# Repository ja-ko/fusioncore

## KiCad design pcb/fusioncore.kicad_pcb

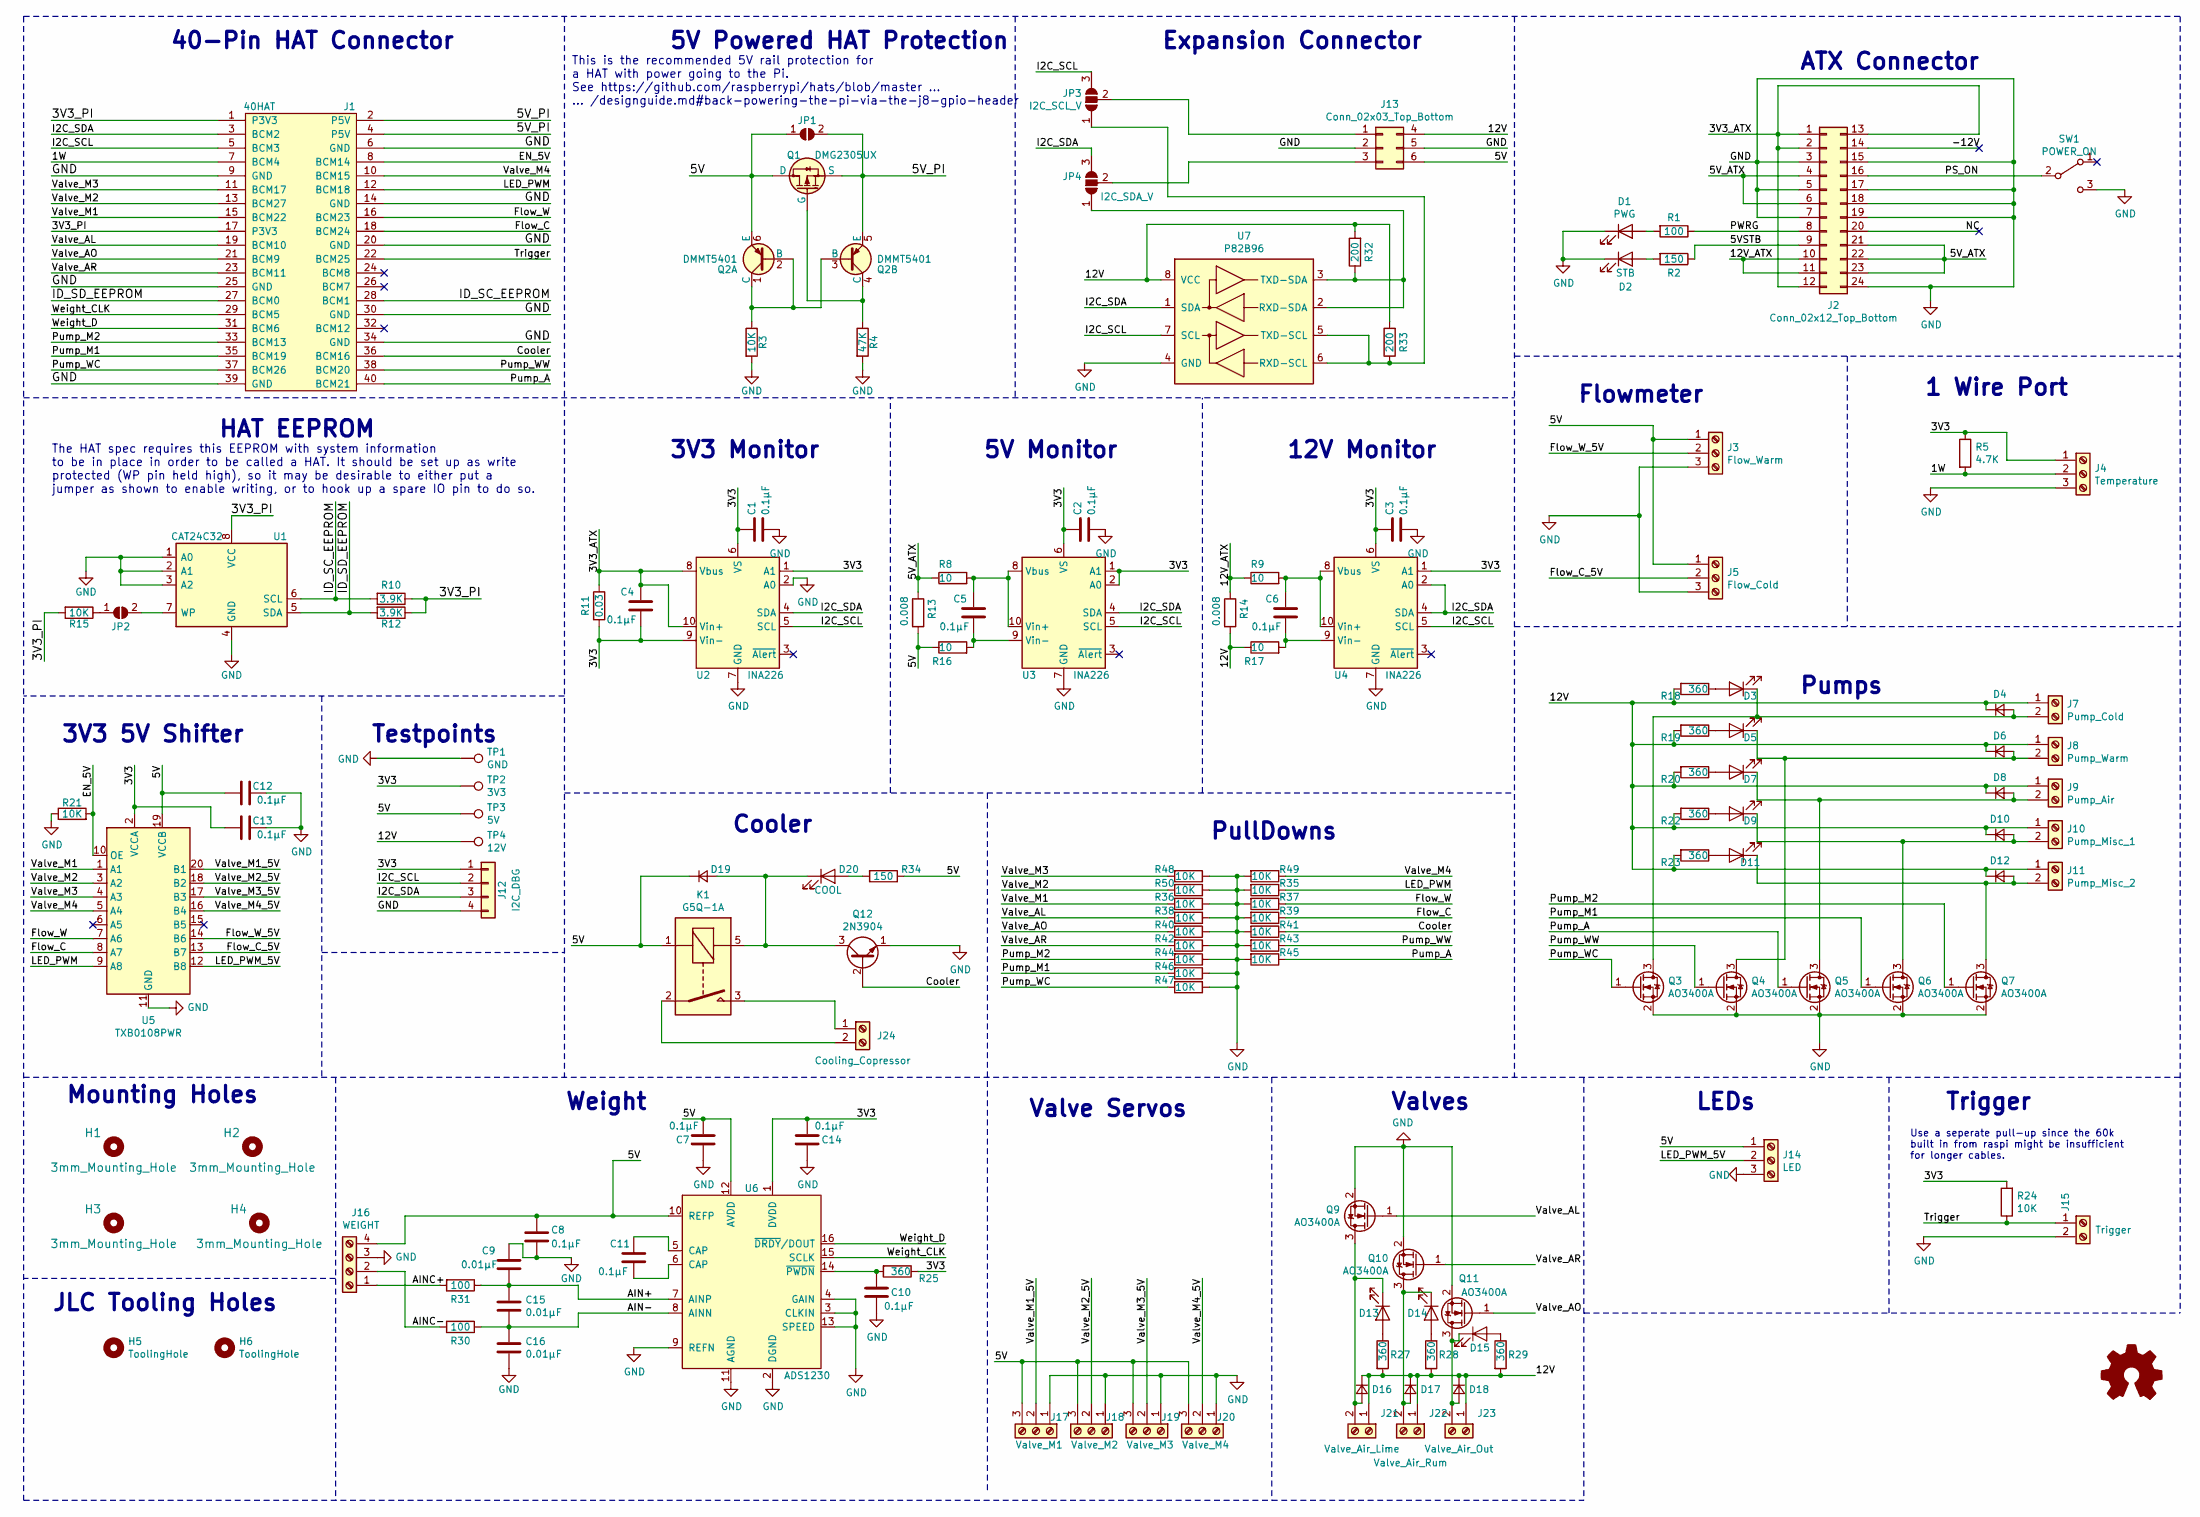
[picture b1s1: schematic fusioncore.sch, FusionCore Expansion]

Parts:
C1, C2, C3, C4, C5, C6, C7, C8, C10, C11, C12, C13, C14: 0.1μF; C_0805_2012Metric_Pad1.15x1.40mm_HandSolder; LCSC C49678
C9, C15, C16: 0.01μF; C_0402_1005Metric; LCSC C15195
D1: PWG; LED_0603_1608Metric_Pad1.05x0.95mm_HandSolder; LCSC C72043
D2: STB; LED_0805_2012Metric_Pad1.15x1.40mm_HandSolder; LCSC C2296
D3, D5, D7, D9, D11, D13, D14, D15: LED; LED_0603_1608Metric_Pad1.05x0.95mm_HandSolder; LCSC C72041
D4, D6, D8, D10, D12: D_Small; D_SMA; LCSC C22452
D16, D17, D18, D19: D; D_SMA; LCSC C22452
D20: COOL; LED_0805_2012Metric_Pad1.15x1.40mm_HandSolder; LCSC C2296
H1, H2, H3, H4: 3mm_Mounting_Hole; NPTH_3mm_ID
H5, H6: ToolingHole; JLC_Tooling_Hole
J1: 40HAT; PinSocket_2x20_P2.54mm_Vertical; Digikey 952-2150-ND‎
J2: Conn_02x12_Top_Bottom; Molex_Mini-Fit_Jr_5566-24A_2x12_P4.20mm_Vertical; Digikey WM3811-ND‎
J3: Flow_Warm; TerminalBlock_Phoenix_PT-1,5-3-5.0-H_1x03_P5.00mm_Horizontal; Digikey 277-1578-ND‎
J4: Temperature; TerminalBlock_Phoenix_PT-1,5-2-3.5-H_1x03_P3.50mm_Diagonal; Digikey 277-1780-ND
J5: Flow_Cold; TerminalBlock_Phoenix_PT-1,5-3-5.0-H_1x03_P5.00mm_Horizontal; Digikey 277-1578-ND‎
J7: Pump_Cold; TerminalBlock_Phoenix_PT-1,5-2-5.0-H_1x02_P5.00mm_Horizontal; Digikey 277-1667-ND
J8: Pump_Warm; TerminalBlock_Phoenix_PT-1,5-2-5.0-H_1x02_P5.00mm_Horizontal; Digikey 277-1667-ND
J9: Pump_Air; TerminalBlock_Phoenix_PT-1,5-2-5.0-H_1x02_P5.00mm_Horizontal; Digikey 277-1667-ND
J10: Pump_Misc_1; TerminalBlock_Phoenix_PT-1,5-2-5.0-H_1x02_P5.00mm_Horizontal; Digikey 277-1667-ND
J11: Pump_Misc_2; TerminalBlock_Phoenix_PT-1,5-2-5.0-H_1x02_P5.00mm_Horizontal; Digikey 277-1667-ND
J12: I2C_DBG; PinHeader_1x04_P2.54mm_Vertical; Digikey 732-5317-ND
J13: Conn_02x03_Top_Bottom; Molex_Micro-Fit_3.0_43045-0612_2x03_P3.00mm_Vertical; Digikey WM1791-ND
J14: LED; TerminalBlock_Phoenix_PT-1,5-3-5.0-H_1x03_P5.00mm_Horizontal; Digikey 277-1578-ND‎
J15: Trigger; TerminalBlock_Phoenix_PT-1,5-2-3.5-H_1x02_P3.50mm_Diagonal; Digikey 277-1779-ND
J16: WEIGHT; TerminalBlock_Phoenix_PT-1,5-4-5.0-H_1x04_P5.00mm_Horizontal
J17: Valve_M1; TerminalBlock_Phoenix_PT-1,5-3-5.0-H_1x03_P5.00mm_Horizontal; Digikey 277-1578-ND‎
J18: Valve_M2; TerminalBlock_Phoenix_PT-1,5-3-5.0-H_1x03_P5.00mm_Horizontal; Digikey 277-1578-ND‎
J19: Valve_M3; TerminalBlock_Phoenix_PT-1,5-3-5.0-H_1x03_P5.00mm_Horizontal; Digikey 277-1578-ND‎
J20: Valve_M4; TerminalBlock_Phoenix_PT-1,5-3-5.0-H_1x03_P5.00mm_Horizontal; Digikey 277-1578-ND‎
J21: Valve_Air_Lime; TerminalBlock_Phoenix_PT-1,5-2-5.0-H_1x02_P5.00mm_Horizontal; Digikey 277-1667-ND
J22: Valve_Air_Rum; TerminalBlock_Phoenix_PT-1,5-2-5.0-H_1x02_P5.00mm_Horizontal; Digikey 277-1667-ND
J23: Valve_Air_Out; TerminalBlock_Phoenix_PT-1,5-2-5.0-H_1x02_P5.00mm_Horizontal; Digikey 277-1667-ND
J24: Cooling_Copressor; TerminalBlock_Phoenix_PT-1,5-2-5.0-H_1x02_P5.00mm_Horizontal
JP1, JP2: SolderJumper_2_Open; SolderJumper-2_P1.3mm_Open_Pad1.0x1.5mm
JP3: I2C_SCL_V; SolderJumper-3_P1.3mm_Open_Pad1.0x1.5mm
JP4: I2C_SDA_V; SolderJumper-3_P1.3mm_Open_Pad1.0x1.5mm
K1: G5Q-1A; Relay_SPST_Omron-G5Q-1A; Digikey ‎Z6367-ND‎
Q1: DMG2305UX; SOT-23; LCSC C144153
Q2: DMMT5401; SOT-23-6_Handsoldering; LCSC C154733
Q3, Q4, Q5, Q6, Q7, Q9, Q10, Q11: AO3400A; SOT-23; LCSC C20917
Q12: 2N3904; SOT-23; LCSC C18536
R1, R30, R31: 100; R_0805_2012Metric_Pad1.15x1.40mm_HandSolder; LCSC C17408
R2, R34: 150; R_0805_2012Metric_Pad1.15x1.40mm_HandSolder; LCSC C17471
R3, R15, R21, R24: 10K; R_0805_2012Metric_Pad1.15x1.40mm_HandSolder; LCSC C17414
R4: 47K; R_0805_2012Metric_Pad1.15x1.40mm_HandSolder; LCSC C17713
R5: 4.7K; R_0805_2012Metric_Pad1.15x1.40mm_HandSolder; LCSC C17673
R8, R9, R16, R17: 10; R_0805_2012Metric_Pad1.15x1.40mm_HandSolder; LCSC C17415
R10, R12: 3.9K; R_0805_2012Metric_Pad1.15x1.40mm_HandSolder; LCSC C17614
R11: 0.03; R_0805_2012Metric_Pad1.15x1.40mm_HandSolder; LCSC C247605
R13, R14: 0.008; R_2512_6332Metric_Pad1.52x3.35mm_HandSolder; LCSC C76241
R18, R19, R20, R22, R23, R25, R27, R28, R29: 360; R_0603_1608Metric_Pad1.05x0.95mm_HandSolder; LCSC C25194
R32, R33: 200; R_0805_2012Metric_Pad1.15x1.40mm_HandSolder; LCSC C17540
R35, R36, R37, R38, R39, R40, R41, R42, R43, R44, R45, R46, R47, R48, R49, R50: 10K; R_0402_1005Metric; LCSC C25744
SW1: POWER_ON; SW_CuK_JS202011CQN_DPDT_Straight; Digikey 401-2001-ND
TP1: GND; TestPoint_THTPad_D2.0mm_Drill1.0mm
TP2: 3V3; TestPoint_THTPad_D2.0mm_Drill1.0mm
TP3: 5V; TestPoint_THTPad_D2.0mm_Drill1.0mm
TP4: 12V; TestPoint_THTPad_D2.0mm_Drill1.0mm
U1: CAT24C32; SOIC-8_3.9x4.9mm_P1.27mm; LCSC C81193
U2, U3, U4: INA226; VSSOP-10_3x3mm_P0.5mm; LCSC C49851
U5: TXB0108PWR; TSSOP-20_4.4x6.5mm_P0.65mm; LCSC C53406
U6: ADS1230; TSSOP-16_4.4x5mm_P0.65mm; LCSC C58052
U7: P82B96; SOIC-8_3.9x4.9mm_P1.27mm; LCSC C32103

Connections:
/1W: J1.7 (BCM4), J4.2, R5.2
/3V3: C1.2, C2.2, C3.2, C4.1, C13.2, C14.2, J4.1, J12.1, R5.1, R11.2, R24.2, R25.1, TP2.1, U2.1 (A1), U2.6 (VS), U2.9 (Vin-), U3.1 (A1), U3.2 (A0), U3.6 (VS), U4.1 (A1), U4.6 (VS), U5.2 (VCCA), U6.1 (DVDD)
/3V3_ATX: C4.2, J2.1, J2.2, J2.12, J2.13, R11.1, U2.8 (Vbus), U2.10 (Vin+)
/3V3_PI: J1.1 (P3V3), J1.17 (P3V3), R10.1, R12.1, R15.2, U1.8 (VCC)
/5V: C7.2, C8.2, C12.2, D19.1 (K), J3.1, J5.1, J13.6, J14.1, J16.4, J17.3, J18.3, J19.3, J20.3, JP1.1 (A), K1.1, Q1.3 (D), Q2.6 (E), R13.2, R16.1, R34.1, TP3.1, U5.19 (VCCB), U6.10 (REFP), U6.12 (AVDD)
/5VSTB: J2.9, R2.1
/5V_ATX: J2.4, J2.6, J2.21, J2.22, J2.23, R8.1, R13.1
/5V_PI: J1.2 (P5V), J1.4 (P5V), JP1.2 (B), Q1.2 (S), Q2.5 (E)
/12V: D4.1 (K), D6.1 (K), D8.1 (K), D10.1 (K), D12.1 (K), D16.1 (K), D17.1 (K), D18.1 (K), J7.1, J8.1, J9.1, J10.1, J11.1, J13.4, J21.1, J22.1, J23.1, R14.2, R17.1, R18.2, R19.2, R20.2, R22.2, R23.2, R27.2, R28.2, R29.2, R32.2, R33.2, TP4.1, U7.8 (VCC)
/12V_ATX: J2.10, J2.11, R9.1, R14.1
/AIN+: C9.1, C15.2, R31.1, U6.7 (AINP)
/AIN-: C15.1, C16.2, R30.1, U6.8 (AINN)
/AINC+: J16.1, R31.2
/AINC-: J16.2, R30.2
/Cooler: J1.36 (BCM16), Q12.2 (B), R41.1
/EN_5V: J1.8 (BCM14), R21.2, U5.10 (OE)
/Flow_C: J1.18 (BCM24), R39.1, U5.8 (A7)
/Flow_C_5V: J5.2, U5.13 (B7)
/Flow_W: J1.16 (BCM23), R37.1, U5.7 (A6)
/Flow_W_5V: J3.2, U5.14 (B6)
/I2C_SCL: J1.5 (BCM3), J12.2, JP3.3 (B), U2.5 (SCL), U3.5 (SCL), U4.5 (SCL), U7.7 (SCL)
/I2C_SDA: J1.3 (BCM2), J12.3, JP4.3 (B), U2.4 (SDA), U3.4 (SDA), U4.2 (A0), U4.4 (SDA), U7.1 (SDA)
/ID_SC_EEPROM: J1.28 (BCM1), R10.2, U1.6 (SCL)
/ID_SD_EEPROM: J1.27 (BCM0), R12.2, U1.5 (SDA)
/LED_PWM: J1.12 (BCM18), R35.1, U5.9 (A8)
/LED_PWM_5V: J14.2, U5.12 (B8)
/PS_ON: J2.16, SW1.2 (B)
/PWRG: J2.8, R1.1
/Pump_A: J1.40 (BCM21), Q5.1 (G), R45.1
/Pump_M1: J1.35 (BCM19), Q6.1 (G), R46.2
/Pump_M2: J1.33 (BCM13), Q7.1 (G), R44.2
/Pump_WC: J1.37 (BCM26), Q3.1 (G), R47.2
/Pump_WW: J1.38 (BCM20), Q4.1 (G), R43.1
/Trigger: J1.22 (BCM25), J15.1, R24.1
/Valve_AL: J1.19 (BCM10), Q9.1 (G), R38.2
/Valve_AO: J1.21 (BCM9), Q11.1 (G), R40.2
/Valve_AR: J1.23 (BCM11), Q10.1 (G), R42.2
/Valve_M1: J1.15 (BCM22), R36.2, U5.1 (A1)
/Valve_M1_5V: J17.2, U5.20 (B1)
/Valve_M2: J1.13 (BCM27), R50.2, U5.3 (A2)
/Valve_M2_5V: J18.2, U5.18 (B2)
/Valve_M3: J1.11 (BCM17), R48.2, U5.4 (A3)
/Valve_M3_5V: J19.2, U5.17 (B3)
/Valve_M4: J1.10 (BCM15), R49.1, U5.5 (A4)
/Valve_M4_5V: J20.2, U5.16 (B4)
/Weight_CLK: J1.29 (BCM5), U6.15 (SCLK)
/Weight_D: J1.31 (BCM6), U6.16 (~DRDY~/DOUT)
GND: C1.1, C2.1, C3.1, C7.1, C8.1, C9.2, C10.1, C12.1, C13.1, C14.1, C16.1, D1.1 (K), D2.1 (K), J1.6 (GND), J1.9 (GND), J1.14 (GND), J1.20 (GND), J1.25 (GND), J1.30 (GND), J1.34 (GND), J1.39 (GND), J2.3, J2.5, J2.7, J2.15, J2.17, J2.18, J2.19, J2.24, J3.3, J4.3, J5.3, J12.4, J13.2, J13.5, J14.3, J15.2, J16.3, J17.1, J18.1, J19.1, J20.1, Q3.2 (S), Q4.2 (S), Q5.2 (S), Q6.2 (S), Q7.2 (S), Q9.2 (S), Q10.2 (S), Q11.2 (S), Q12.1 (E), R3.2, R4.2, R21.1, R35.2, R36.1, R37.2, R38.1, R39.2, R40.1, R41.2, R42.1, R43.2, R44.1, R45.2, R46.1, R47.1, R48.1, R49.2, R50.1, SW1.3 (C), TP1.1, U1.1 (A0), U1.2 (A1), U1.3 (A2), U1.4 (GND), U2.2 (A0), U2.7 (GND), U3.7 (GND), U4.7 (GND), U5.11 (GND), U6.2 (DGND), U6.3 (CLKIN), U6.4 (GAIN), U6.9 (REFN), U6.11 (AGND), U6.13 (SPEED), U7.4 (GND)
unnamed: C5.1, R16.2, U3.9 (Vin-)
unnamed: C5.2, R8.2, U3.8 (Vbus), U3.10 (Vin+)
unnamed: C6.1, R17.2, U4.9 (Vin-)
unnamed: C6.2, R9.2, U4.8 (Vbus), U4.10 (Vin+)
unnamed: C10.2, R25.2, U6.14 (~PWDN)
unnamed: C11.1, U6.5 (CAP)
unnamed: C11.2, U6.6 (CAP)
unnamed: D1.2 (A), R1.2
unnamed: D2.2 (A), R2.2
unnamed: D3.1 (K), D4.2 (A), J7.2, Q3.3 (D)
unnamed: D3.2 (A), R18.1
unnamed: D5.1 (K), D6.2 (A), J8.2, Q4.3 (D)
unnamed: D5.2 (A), R19.1
unnamed: D7.1 (K), D8.2 (A), J9.2, Q5.3 (D)
unnamed: D7.2 (A), R20.1
unnamed: D9.2 (A), R22.1
unnamed: D9.1 (K), D10.2 (A), J10.2, Q6.3 (D)
unnamed: D11.1 (K), D12.2 (A), J11.2, Q7.3 (D)
unnamed: D11.2 (A), R23.1
unnamed: D13.1 (K), D16.2 (A), J21.2, Q9.3 (D)
unnamed: D13.2 (A), R27.1
unnamed: D14.1 (K), D17.2 (A), J22.2, Q10.3 (D)
unnamed: D14.2 (A), R28.1
unnamed: D15.1 (K), D18.2 (A), J23.2, Q11.3 (D)
unnamed: D15.2 (A), R29.1
unnamed: D19.2 (A), D20.1 (K), K1.5, Q12.3 (C)
unnamed: D20.2 (A), R34.2
unnamed: J13.1, JP3.2 (C)
unnamed: J13.3, JP4.2 (C)
unnamed: J24.1, K1.3
unnamed: J24.2, K1.2
unnamed: JP2.1 (A), R15.1
unnamed: JP2.2 (B), U1.7 (WP)
unnamed: JP3.1 (A), R33.1, U7.5 (TXD-SCL), U7.6 (RXD-SCL)
unnamed: JP4.1 (A), R32.1, U7.2 (RXD-SDA), U7.3 (TXD-SDA)
unnamed: Q1.1 (G), Q2.4 (C), R4.1
unnamed: Q2.1 (C), Q2.2 (B), Q2.3 (B), R3.1

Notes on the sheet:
5V Powered HAT Protection
This is the recommended 5V rail protection for a HAT with power going to the Pi. See https://github.com/raspberrypi/hats/blob/master ... ... /designguide.md#back-powering-the-pi-via-the-j8-gpio-header
HAT EEPROM
Mounting Holes
40-Pin HAT Connector
The HAT spec requires this EEPROM with system information to be in place in order to be called a HAT. It should be set up as write protected (WP pin held high), so it may be desirable to either put a jumper as shown to enable writing, or to hook up a spare IO pin to do so.
ATX Connector
1 Wire Port
Pumps
Valves
LEDs
Flowmeter
Weight
Use a seperate pull-up since the 60k built in from raspi might be insufficient for longer cables.
Trigger
3V3 Monitor
Testpoints
3V3 5V Shifter
Valve Servos
Expansion Connector
JLC Tooling Holes
5V Monitor
12V Monitor
Cooler
PullDowns

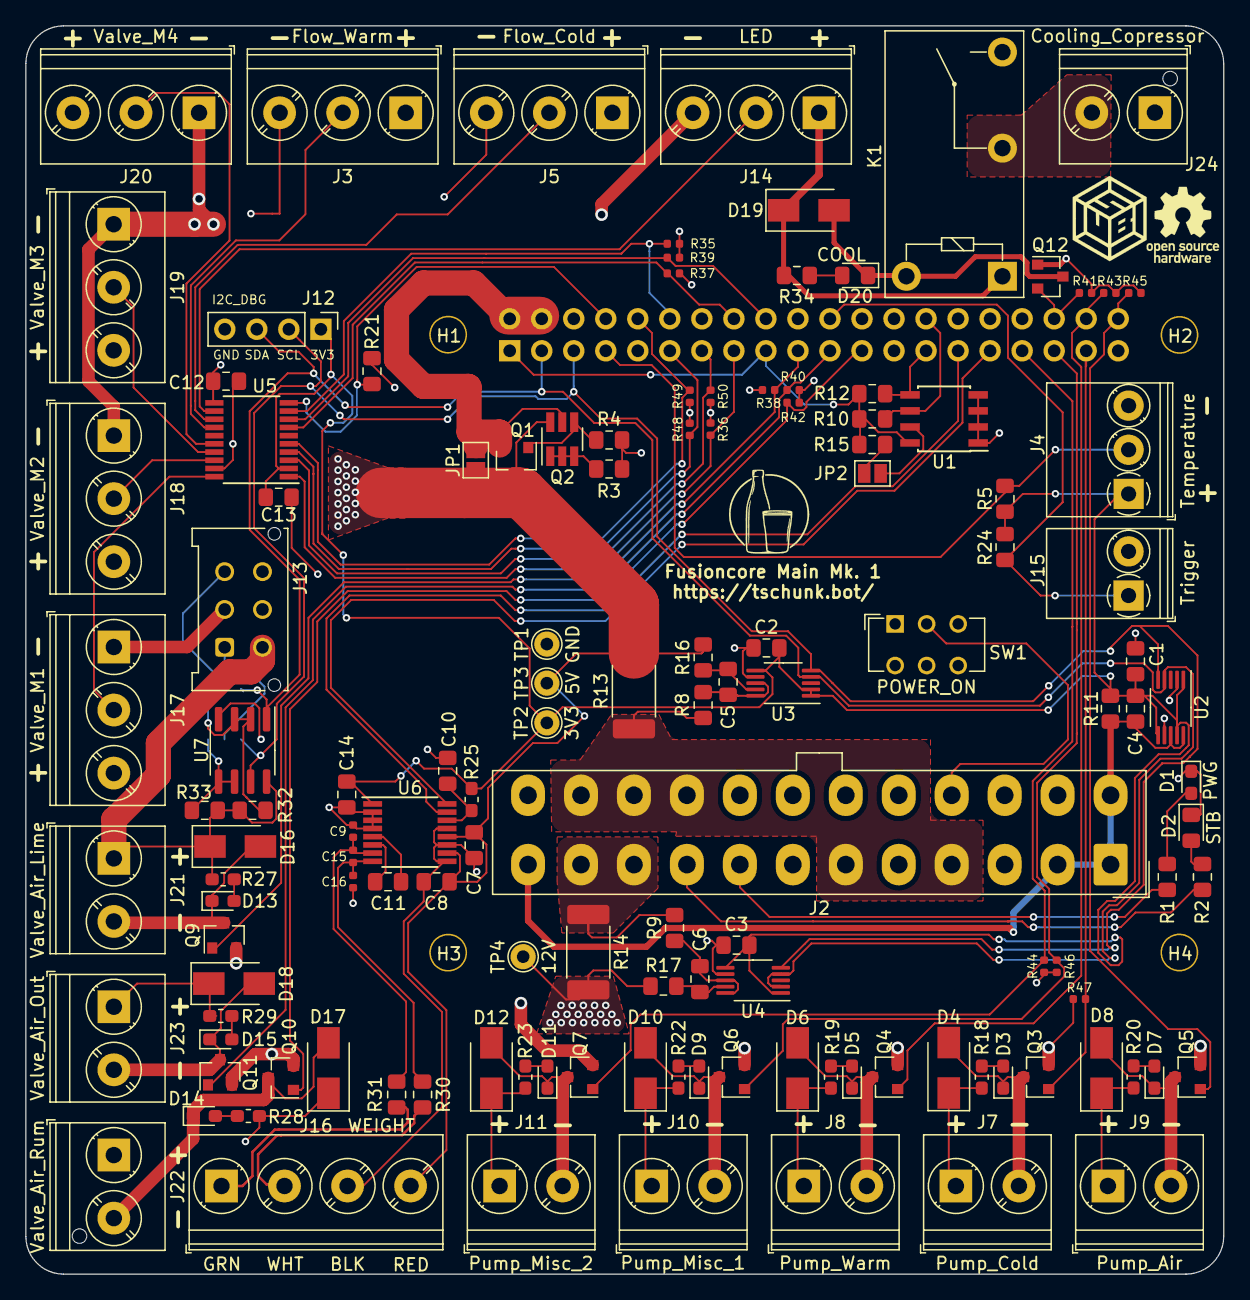
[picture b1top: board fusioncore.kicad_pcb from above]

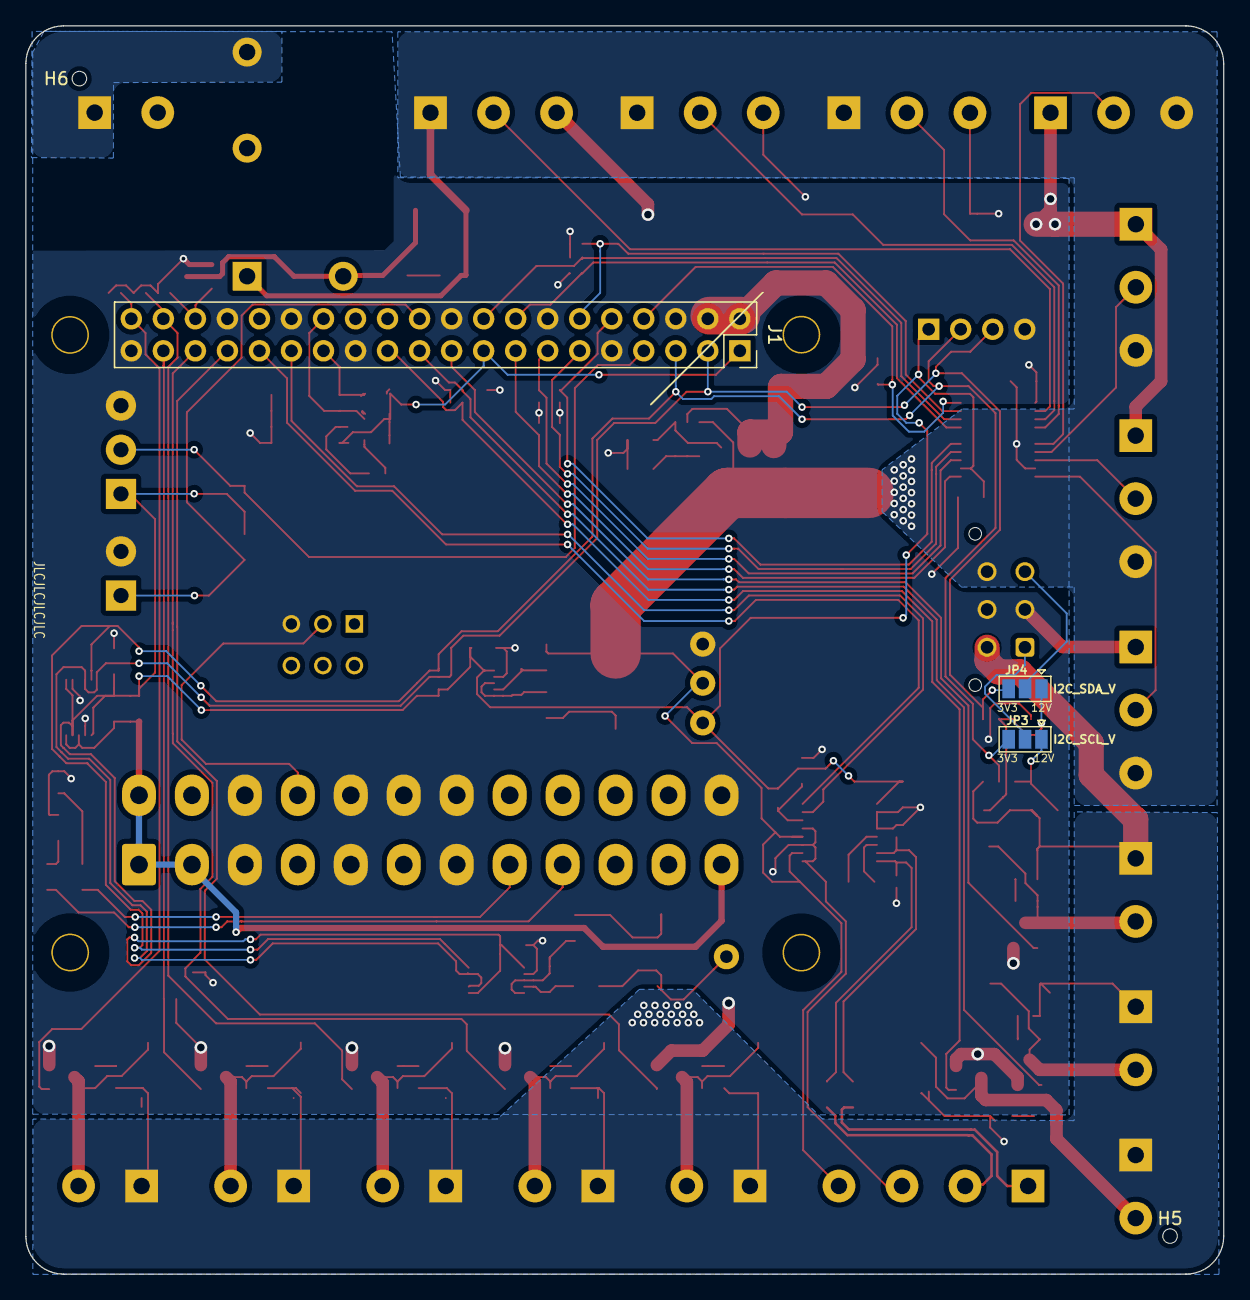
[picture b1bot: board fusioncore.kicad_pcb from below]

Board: 2 copper layers, 95.0 x 99.0 mm, 140 parts (5 on the bottom side), 85 nets.

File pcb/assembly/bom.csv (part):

Reference, Value, Footprint, Datasheet, LCSC, Digikey, Address
"H1","3mm_Mounting_Hole","project_footprints:NPTH_3mm_ID",""
"H2","3mm_Mounting_Hole","project_footprints:NPTH_3mm_ID",""
"H3","3mm_Mounting_Hole","project_footprints:NPTH_3mm_ID",""
"H4","3mm_Mounting_Hole","project_footprints:NPTH_3mm_ID",""
"J1","40HAT","Connector_PinSocket_2.54mm:PinSocket_2x20_P2.54mm_Vertical",""
"Q1","DMG2305UX","Package_TO_SOT_SMD:SOT-23","","C144153","",""
"Q2","DMMT5401","Package_TO_SOT_SMD:SOT-23-6_Handsoldering","","C154733","",""
"R3","10K","Resistor_SMD:R_0805_2012Metric_Pad1.15x1.40mm_HandSolder","","C17414","",""
"R4","47K","Resistor_SMD:R_0805_2012Metric_Pad1.15x1.40mm_HandSolder","","C17713","",""
"U1","CAT24C32","Package_SOIC:SOIC-8_3.9x4.9mm_P1.27mm","https://datasheet.lcsc.com/szlcsc/1809291220_ON-Semicon-CAT2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","C81193","",""
"R12","3.9K","Resistor_SMD:R_0805_2012Metric_Pad1.15x1.40mm_HandSolder","","C17614","",""
"R10","3.9K","Resistor_SMD:R_0805_2012Metric_Pad1.15x1.40mm_HandSolder","","C17614","",""
"R15","10K","Resistor_SMD:R_0805_2012Metric_Pad1.15x1.40mm_HandSolder","","C17414","",""
"J4","Temperature","project_footprints:TerminalBlock_Phoenix_PT-1,5-2-3.5-H_1x03_P3.50mm_Diagonal","https://media.digikey.com/pdf/Data%20Sheets/Phoenix%20Contac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",""," 277-1780-ND",""
"R5","4.7K","Resistor_SMD:R_0805_2012Metric_Pad1.15x1.40mm_HandSolder","~","C17673","",""
"J7","Pump_Cold","TerminalBlock_Phoenix:TerminalBlock_Phoenix_PT-1,5-2-5.0-H_1x02_P5.00mm_Horizontal","https://media.digikey.com/pdf/Data%20Sheets/Phoenix%20Contac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","","277-1667-ND",""
"J8","Pump_Warm","TerminalBlock_Phoenix:TerminalBlock_Phoenix_PT-1,5-2-5.0-H_1x02_P5.00mm_Horizontal","https://media.digikey.com/pdf/Data%20Sheets/Phoenix%20Contac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","","277-1667-ND",""
"J9","Pump_Air","TerminalBlock_Phoenix:TerminalBlock_Phoenix_PT-1,5-2-5.0-H_1x02_P5.00mm_Horizontal","https://media.digikey.com/pdf/Data%20Sheets/Phoenix%20Contac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","","277-1667-ND",""
"J10","Pump_Misc_1","TerminalBlock_Phoenix:TerminalBlock_Phoenix_PT-1,5-2-5.0-H_1x02_P5.00mm_Horizontal","https://media.digikey.com/pdf/Data%20Sheets/Phoenix%20Contac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","","277-1667-ND",""
"J11","Pump_Misc_2","TerminalBlock_Phoenix:TerminalBlock_Phoenix_PT-1,5-2-5.0-H_1x02_P5.00mm_Horizontal","https://media.digikey.com/pdf/Data%20Sheets/Phoenix%20Contac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","","277-1667-ND",""
"Q7","AO3400A","Package_TO_SOT_SMD:SOT-23","https://datasheet.lcsc.com/szlcsc/Alpha-Omega-Semicon-AOS-AO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","C20917","",""
"Q6","AO3400A","Package_TO_SOT_SMD:SOT-23","https://datasheet.lcsc.com/szlcsc/Alpha-Omega-Semicon-AOS-AO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","C20917","",""
"Q5","AO3400A","Package_TO_SOT_SMD:SOT-23","https://datasheet.lcsc.com/szlcsc/Alpha-Omega-Semicon-AOS-AO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","C20917","",""
"Q4","AO3400A","Package_TO_SOT_SMD:SOT-23","https://datasheet.lcsc.com/szlcsc/Alpha-Omega-Semicon-AOS-AO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","C20917","",""
"Q3","AO3400A","Package_TO_SOT_SMD:SOT-23","https://datasheet.lcsc.com/szlcsc/Alpha-Omega-Semicon-AOS-AO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","C20917","",""
"J23","Valve_Air_Out","TerminalBlock_Phoenix:TerminalBlock_Phoenix_PT-1,5-2-5.0-H_1x02_P5.00mm_Horizontal","https://media.digikey.com/pdf/Data%20Sheets/Phoenix%20Contac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","","277-1667-ND",""
"J22","Valve_Air_Rum","TerminalBlock_Phoenix:TerminalBlock_Phoenix_PT-1,5-2-5.0-H_1x02_P5.00mm_Horizontal","https://media.digikey.com/pdf/Data%20Sheets/Phoenix%20Contac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","","277-1667-ND",""
"J21","Valve_Air_Lime","TerminalBlock_Phoenix:TerminalBlock_Phoenix_PT-1,5-2-5.0-H_1x02_P5.00mm_Horizontal","https://media.digikey.com/pdf/Data%20Sheets/Phoenix%20Contac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","","277-1667-ND",""
"Q11","AO3400A","Package_TO_SOT_SMD:SOT-23","https://datasheet.lcsc.com/szlcsc/Alpha-Omega-Semicon-AOS-AO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","C20917","",""
"Q10","AO3400A","Package_TO_SOT_SMD:SOT-23","https://datasheet.lcsc.com/szlcsc/Alpha-Omega-Semicon-AOS-AO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","C20917","",""
"Q9","AO3400A","Package_TO_SOT_SMD:SOT-23","https://datasheet.lcsc.com/szlcsc/Alpha-Omega-Semicon-AOS-AO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","C20917","",""
"D4","D_Small","Diode_SMD:D_SMA","~","C22452","",""
"D6","D_Small","Diode_SMD:D_SMA","~","C22452","",""
"D8","D_Small","Diode_SMD:D_SMA","~","C22452","",""
"D10","D_Small","Diode_SMD:D_SMA","~","C22452","",""
"D12","D_Small","Diode_SMD:D_SMA","~","C22452","",""
"D18","D","Diode_SMD:D_SMA","~","C22452","",""
"D17","D","Diode_SMD:D_SMA","~","C22452","",""
"D16","D","Diode_SMD:D_SMA","~","C22452","",""
"J14","LED","TerminalBlock_Phoenix:TerminalBlock_Phoenix_PT-1,5-3-5.0-H_1x03_P5.00mm_Horizontal","https://media.digikey.com/pdf/Data%20Sheets/Phoenix%20Contac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"
"J3","Flow_Warm","TerminalBlock_Phoenix:TerminalBlock_Phoenix_PT-1,5-3-5.0-H_1x03_P5.00mm_Horizontal","https://media.digikey.com/pdf/Data%20Sheets/Phoenix%20Contac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"
"J5","Flow_Cold","TerminalBlock_Phoenix:TerminalBlock_Phoenix_PT-1,5-3-5.0-H_1x03_P5.00mm_Horizontal","https://media.digikey.com/pdf/Data%20Sheets/Phoenix%20Contac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"
"R6","10K","Resistor_SMD:R_0805_2012Metric_Pad1.15x1.40mm_HandSolder","~","C17414","",""
"R7","10K","Resistor_SMD:R_0805_2012Metric_Pad1.15x1.40mm_HandSolder","~","C17414","",""
"J2","Conn_02x12_Top_Bottom","Connector_Molex:Molex_Mini-Fit_Jr_5566-24A_2x12_P4.20mm_Vertical","~"
"R1","100","Resistor_SMD:R_0805_2012Metric_Pad1.15x1.40mm_HandSolder","~","C17408","",""
"D1","PWG","LED_SMD:LED_0603_1608Metric_Pad1.05x0.95mm_HandSolder","~","C72043","",""
"R2","150","Resistor_SMD:R_0805_2012Metric_Pad1.15x1.40mm_HandSolder","~","C17471","",""
"D2","STB","LED_SMD:LED_0805_2012Metric_Pad1.15x1.40mm_HandSolder","~","C2296","",""
"SW1","POWER_ON","Button_Switch_THT:SW_CuK_JS202011CQN_DPDT_Straight","https://dznh3ojzb2azq.cloudfront.net/products/Slide/JS/docum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","","401-2001-ND",""
"R30","100","Resistor_SMD:R_0805_2012Metric_Pad1.15x1.40mm_HandSolder","~","C17408","",""
"R31","100","Resistor_SMD:R_0805_2012Metric_Pad1.15x1.40mm_HandSolder","~","C17408","",""
"C11","0.1μF","Capacitor_SMD:C_0805_2012Metric_Pad1.15x1.40mm_HandSolder","~","C49678","",""
"C8","0.1μF","Capacitor_SMD:C_0805_2012Metric_Pad1.15x1.40mm_HandSolder","~","C49678","",""
"R24","10K","Resistor_SMD:R_0805_2012Metric_Pad1.15x1.40mm_HandSolder","~","C17414","",""
"J15","Trigger","project_footprints:TerminalBlock_Phoenix_PT-1,5-2-3.5-H_1x02_P3.50mm_Diagonal","https://media.digikey.com/pdf/Data%20Sheets/Phoenix%20Contac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",""," 277-1779-ND",""
"R11","0.03","Resistor_SMD:R_0805_2012Metric_Pad1.15x1.40mm_HandSolder","~","C247605","",""
"R13","0.008","Resistor_SMD:R_2512_6332Metric_Pad1.52x3.35mm_HandSolder","~","C76241","",""
"TP2","3V3","TestPoint:TestPoint_THTPad_D2.0mm_Drill1.0mm","~"
"TP3","5V","TestPoint:TestPoint_THTPad_D2.0mm_Drill1.0mm","~"
"TP4","12V","TestPoint:TestPoint_THTPad_D2.0mm_Drill1.0mm","~"
"TP1","GND","TestPoint:TestPoint_THTPad_D2.0mm_Drill1.0mm","~"
"J20","Valve_M4","TerminalBlock_Phoenix:TerminalBlock_Phoenix_PT-1,5-3-5.0-H_1x03_P5.00mm_Horizontal","https://media.digikey.com/pdf/Data%20Sheets/Phoenix%20Contac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"
"J19","Valve_M3","TerminalBlock_Phoenix:TerminalBlock_Phoenix_PT-1,5-3-5.0-H_1x03_P5.00mm_Horizontal","https://media.digikey.com/pdf/Data%20Sheets/Phoenix%20Contac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"
"J18","Valve_M2","TerminalBlock_Phoenix:TerminalBlock_Phoenix_PT-1,5-3-5.0-H_1x03_P5.00mm_Horizontal","https://media.digikey.com/pdf/Data%20Sheets/Phoenix%20Contac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"
"J17","Valve_M1","TerminalBlock_Phoenix:TerminalBlock_Phoenix_PT-1,5-3-5.0-H_1x03_P5.00mm_Horizontal","https://media.digikey.com/pdf/Data%20Sheets/Phoenix%20Contac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"
"R29","360","Resistor_SMD:R_0603_1608Metric_Pad1.05x0.95mm_HandSolder","https://datasheet.lcsc.com/szlcsc/Uniroyal-Elec-0603WAF3600T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","C25194","",""
"D15","LED","LED_SMD:LED_0603_1608Metric_Pad1.05x0.95mm_HandSolder","https://datasheet.lcsc.com/szlcsc/Everlight-Elec-19-217-BHC-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","C72041","",""
"R28","360","Resistor_SMD:R_0603_1608Metric_Pad1.05x0.95mm_HandSolder","https://datasheet.lcsc.com/szlcsc/Uniroyal-Elec-0603WAF3600T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","C25194","",""
"D14","LED","LED_SMD:LED_0603_1608Metric_Pad1.05x0.95mm_HandSolder","https://datasheet.lcsc.com/szlcsc/Everlight-Elec-19-217-BHC-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","C72041","",""
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
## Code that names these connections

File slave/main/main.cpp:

#include <string.h>
#include "freertos/FreeRTOS.h"
#include "freertos/task.h"
#include <stdio.h>
#include <driver/i2c.h>
#include "esp_log.h"
#include "driver/i2c.h"
#include "sdkconfig.h"
#include "driver/gpio.h"
#include <vector>
#include <map>
#include <soc/i2c_struct.h>
#include "math.h"
#include "devices.h"


static const char *TAG = "fusiocore-slave";

#define I2C_SDA GPIO_NUM_32 //red
#define I2C_SCL GPIO_NUM_33
#define I2C_ADDR 0x23

#define I2C_RX_BUF_LEN 512
#define I2C_TX_BUF_LEN 512
#define DATA_BUFFER_LEN 1024

#define I2C_PORT I2C_NUM_0

#define TRIGGER_PIN GPIO_NUM_17

static float trigger_timestamp = 0.0f;

typedef float (*measurement_t)();
std::vector<measurement_t> measurement_funcs;
typedef void (*command_t)();
std::map<uint8_t, command_t> command_funcs;

extern "C" {
    void app_main();
}


esp_err_t i2c_slave_init() {
    i2c_config_t config;
    config.sda_io_num = I2C_SDA;
    config.sda_pullup_en = GPIO_PULLUP_ENABLE;
    config.scl_io_num = I2C_SCL;
    config.scl_pullup_en = GPIO_PULLUP_ENABLE;
    config.mode = I2C_MODE_SLAVE;
    config.slave.addr_10bit_en = 0;
    config.slave.slave_addr = I2C_ADDR;
    i2c_param_config(I2C_PORT, &config);
    return i2c_driver_install(I2C_PORT, config.mode, I2C_RX_BUF_LEN, I2C_TX_BUF_LEN, 0);
}

void i2c_loop(void* arg) {
    int size;
    uint8_t* data = (uint8_t *)malloc(DATA_BUFFER_LEN);
    uint8_t cur_register = 0;

    while(1) {
        size = i2c_slave_read_buffer(I2C_PORT, data, DATA_BUFFER_LEN, 1);

        if(size < sizeof(uint8_t)) { // no data received
            continue;
        }

        cur_register = data[0];
        ESP_LOGI(TAG, "Received %u bytes, value: %d", size, cur_register);

        //break;
    }
}


void i2c_read_loop(void* arg) {
    int size;
    auto* data = (uint8_t *)malloc(DATA_BUFFER_LEN);


    while(true) {
        size = i2c_slave_read_buffer(I2C_PORT, data, DATA_BUFFER_LEN, 1);

        if (size < sizeof(uint8_t)) { // no data received
            continue;
        }

        if(size == sizeof(uint8_t)) {
            if(*data == 0) {
                ESP_LOGD(TAG, "Skipping I2C command 0x0");
                // master uses 0 as register, we dont support register, so skip this
                continue;
            }
            ESP_LOGD(TAG, "Handling I2C command 0x%x", *data);
            auto it = command_funcs.find(*data);
            if(it != command_funcs.end()) {
                it->second();
            }


        }


    }
}


/*
 * Update a cache with the newest measurements from measurement_funcs
 */
void measure_loop(void* arg) {
    setup_outgoing_gpios();
    setup_temp_sensor();
    while(1) {
        vTaskDelay(1000 / portTICK_RATE_MS);
    }
}

/*
 * These commands should return immediately. You can time consuming tasks in measure_loop() and store the results in a
 * cache. Return just the cached value from here.
 */
float sinus() {
    auto cur_time = (float) (esp_timer_get_time() / 10000000.0f);
    return sin(cur_time);
}

float last_buzzer() {
    return trigger_timestamp;
}

float flow_warm() {
    return 5.0f;
}

float flow_cold() {
    return 5.0f;
}

float temp_mate() {
    return 17.0f;
}

void write_tx_buffer() {
    uint8_t tx_size = measurement_funcs.size() * sizeof(float);
    i2c_slave_write_buffer(I2C_PORT, reinterpret_cast<uint8_t *>(&tx_size), sizeof(uint8_t), 1);
    ESP_LOGD(TAG, "Header: %d", tx_size);
    for(auto & measurement_func : measurement_funcs) {
        float value = measurement_func();
        int written = i2c_slave_write_buffer(I2C_PORT, (uint8_t*)(&value), sizeof(float), 1);
        if(written != sizeof(float)) {
            ESP_LOGE(TAG, "Failed to write float to tx buffer.");
        }
    }
}

void register_command(uint8_t opcode, command_t command) {
    command_funcs.insert(std::pair<uint8_t, command_t>(opcode, command));
}

void trigger_pressed(void* arg) {
    trigger_timestamp = (float)esp_timer_get_time();
    //ESP_LOGI(TAG, "CRASH!!");
}

void setup_gpio() {
    gpio_install_isr_service(0);
    gpio_set_direction(TRIGGER_PIN, GPIO_MODE_INPUT);
    gpio_pulldown_en(TRIGGER_PIN);
    gpio_pullup_dis(TRIGGER_PIN);
    gpio_isr_handler_add(TRIGGER_PIN, trigger_pressed, nullptr);
    gpio_set_intr_type(TRIGGER_PIN, GPIO_INTR_POSEDGE);
    gpio_intr_enable(TRIGGER_PIN);
}

void reset() {
    ESP_LOGW(TAG, "Restarting ESP cause of reset()");
    esp_restart();
}


void app_main() {
    ESP_LOGI(TAG, "Nabend!");

    setup_gpio();


    measurement_funcs.push_back(sinus);
    measurement_funcs.push_back(last_buzzer);
    measurement_funcs.push_back(flow_warm);
    measurement_funcs.push_back(flow_cold);
    measurement_funcs.push_back(temp_mate);

    register_command(0x1, write_tx_buffer);
    register_command(0x2, air_enable);
    register_command(0x3, air_disable);
    register_command(0x4, valve_alc_open);
    register_command(0x5, valve_alc_close);
    register_command(0x6, valve_lemon_open);
    register_command(0x7, valve_lemon_close);
    register_command(0x8, valve_air_open);
    register_command(0x9, valve_air_close);
    register_command(0xa, pump_warm_enable);
    register_command(0xb, pump_warm_disable);
    register_command(0xc, compressor_enable);
    register_command(0xd, compressor_disable);


    register_command(0xff, reset);

    ESP_ERROR_CHECK(i2c_slave_init());


    xTaskCreate(i2c_read_loop, "i2c_read_loop", 1024 * 2, (void *)0, 10, NULL);
    xTaskCreate(measure_loop, "measure_loop", 1024 * 2, (void *)0, 10, NULL);


}

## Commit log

2019-12-11 Empty project template
2019-12-16 First simple I2C master side
2019-12-21 WIP, Commit not to late, commit often!
2019-12-28 WIP. Stuff done before/during congress
2020-01-05 Added WIP pcb
2020-01-08 Working on PCB schematic
2020-01-12 Working on the layout of pcb
2020-01-13 Almost done with PCB
2020-01-13 Changed Hx711 transistor
2020-01-13 Minor stuff.
2020-01-13 Increased the number of vias for 12V power supply
2020-01-13 Fixed component sizes and rearranged components to match spec
2020-01-13 Added LSCS part numbers
2020-01-26 Minor PCB fixes.
2020-01-26 Added logic level shifter to schema only.
2020-01-26 Organize the schema
2020-01-26 Working on replacing some 2-Port Valves
2020-01-31 Finalized current PCB iteration
2020-01-31 Fixed some more issues on pcb
2020-01-31 Fixed minor issues
2020-01-31 Added more debug and expansion connectors
2020-01-31 Added JLC specific marker
2020-01-31 Fix J23
2020-01-31 Fix some alignments
2020-01-31 Fix clearances of JLC tooling holes
2020-02-01 Replaced LTC2990 with INA226 in schema
2020-02-01 Replaced LTC2990 with INA226 on pcb layout as well
2020-02-01 Cleaned up annotations
2020-02-01 Fixed some alignment issues
2020-02-01 Set I2C Address for INA226s
2020-02-01 Fixed some more alignment issues
2020-02-02 Added license
2020-02-02 Added a P82B96TD for external HighVoltage I2C
2020-02-06 Fixed some minor alignment issues
2020-02-08 Fixed issues from review.
    Swapped diodes for Schottky diodes.
    Changed logic level from HX711 to 3V3
    Moved OE from 5V shifter to raspberry pi.
2020-02-08 Simplified the EEPROM by removing an unecessary jumper
2020-02-17 Added B+/- weight connector
2020-03-01 Added relais for cooling compressor
2020-03-10 Added Relais to board
2020-03-10 Simplified some layouts
2020-03-10 Moved some labels
2020-03-10 Moved some components
2020-03-10 Added subraum logo
2020-03-11 Added and moved some capacitors
2020-03-12 Added LCSC for R30/R31
2020-03-13 Added jumper to allow switching I2C voltage on expansion connector.
2020-03-13 Added labels for I2C Voltage jumper
2020-03-14 Replaces HX711 with ADS1230
2020-03-21 Changed Q2 footprint to handsoldered
2020-03-21 Added missing digikey article numbers
2020-03-21 Ordered for assembly. Rev A
2020-06-07 Started working on Rev B.
    Adds pull-down for MOSFETs. During actual use these are not required.
    However these pull-downs make sure that the MOSFETs can't be damaged
    even when there is no raspberry connected to the board.
    Fixes footprint of U5. Rev A assumed a different pin mapping than the
    actual placed component, so U5 can't be used in Rev A. This fixes the
    pin mapping and reroutes some traces accordingly.
